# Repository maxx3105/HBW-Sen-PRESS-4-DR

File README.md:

# HBW-Sen-PRESS-4-DR

HomeMatic-Wired-Drucksensormodul für Hutschienenmontage

## Überblick

HomeMatic-Wired-Gerät (RS485) zur Überwachung hydraulischer Drücke mit
Industrie-Drucksensoren. Es stellt 4 analoge Sensoreingänge bereit (A0–A3).
Nicht belegte Kanäle werden in der CCU über `Sensortyp = NICHT_BELEGT` abgeschaltet.

### Basiert auf:
- **HBWired** von Thorsten Pferdekaemper: https://github.com/ThorstenPferdekaemper/HBWired
- **HB-UNI-Sen-PRESS** von jp112sdl: https://github.com/jp112sdl/HB-UNI-Sen-PRESS

## Aufbau des Repositories

```
HBW-Sen-PRESS-4-DR/
├── HBW-Sen-PRESS-4-DR/            Arduino-Sketch (Ordnername muss zur .ino passen)
│   ├── HBW-Sen-PRESS-4-DR.ino
│   ├── HBW-Sen-PRESS-4-DR_config_example.h   Pins, EepromPtr, USE_HARDWARE_SERIAL
│   ├── HBWAnalogPRESS.h
│   └── HBWAnalogPRESS.cpp
├── hbw-sen-press-4-dr.xml         CCU-Gerätedefinition (hs485types)
├── HBW-Sen-PRESS-4_Platine1/    KiCad-Projekt Hauptplatine (+ Gerber)
├── HBW-Sen-PRESS-4_Platine2/    KiCad-Projekt zweite Platine (+ Gerber)
├── BUGFIXES.md                  was in v0.01–v0.03 defekt war und warum
└── CLAUDE.md                    kompakter Projektstand / Übergabenotizen
```

## Hardware

### Unterstützte Sensoren
- **0,5 MPa** Hydraulik-Drucksensor (0–5 bar / 0–72,5 PSI)
- **1,2 MPa** Hydraulik-Drucksensor (0–12 bar / 0–174 PSI)

Beide liefern ein Analogsignal von **0,5 V bis 4,5 V**:
- 0,5 V = 0 bar
- 4,5 V = Endwert (5 bzw. 12 bar je nach Sensortyp)

### Bauteile
- **ATmega328P** Mikrocontroller (alternativ Arduino Nano)
- **MAX487E** RS485-Transceiver
- **MC34063AD** Step-Down-Wandler (24 V Bus → 5 V)
- Analogeingänge: A0–A3 in Verwendung

### Merkmale der Platine
- Hutschienenmontage
- Identify-LED zum Auffinden im Verteiler (blinkt, solange `IDENTIFY_LED` in
  den Geräteparametern gesetzt ist)
- RS485-Busanschluss (A, B, GND, +24 V)
- Schraubklemmen für die Sensoren
- ISP-Programmierstecker
- Status-LED
- Taster für Werksreset

## Pinbelegung

| Pin | Funktion |
|-----|----------|
| A0–A3 | Analogeingänge der Drucksensoren |
| D3 | RS485 TXEN |
| A6 | Taster für Werksreset |
| D12 | Identify-LED (optional, auskommentieren wenn nicht bestückt) |
| D13 | Status-LED |

Pins, `EepromPtr` und `USE_HARDWARE_SERIAL` stehen in
`HBW-Sen-PRESS-4-DR_config_example.h`. Bei abweichender Hardware die Datei
kopieren und die Kopie im Sketch einbinden — dann überschreibt sie eine neue
Version aus GitHub nicht.

## Funktionsumfang

### Konfiguration je Kanal (in CCU/FHEM)

| Parameter | Bereich | Vorgabe | Bedeutung |
|-----------|---------|---------|-----------|
| **Sensortyp** | 0.5MPa / 1.2MPa / NICHT_BELEGT | NICHT_BELEGT | Sensortyp wählen oder Kanal abschalten |
| **SEND_DELTA_VALUE** | 0,0–2,54 bar | 0,1 bar | Sendet, sobald sich der Druck um diesen Betrag ändert |
| **OFFSET** | −1,27 bis +1,27 bar | 0,0 bar | Kalibrier-Offset (vorzeichenbehaftet, mit Bias 127 gespeichert) |
| **UPDATE_INTERVAL** | 1–254 s | 30 s | Pause zwischen zwei Messreihen |
| **SEND_MIN_INTERVAL** | 10–3600 s | 30 s | Mindestabstand zwischen zwei Sendungen |
| **SEND_MAX_INTERVAL** | 10–3600 s | 600 s | Spätestens nach dieser Zeit wird gesendet |

Die Obergrenzen vermeiden den Wert aus lauter Einsen (`0xFF` / `0xFFFF`) — der
markiert eine gelöschte EEPROM-Zelle und wird stattdessen auf die Vorgabe
abgebildet.

### Ablauf

1. **Messung**: alle SAMPLE_INTERVAL (3 s) ein ADC-Wert, gemittelt über
   MAX_SAMPLES (4) — ohne blockierendes `delay()`, damit der RS485-Empfang
   reaktionsfähig bleibt. Nach einer vollständigen Messreihe pausiert der Kanal
   für UPDATE_INTERVAL.
2. **Umrechnung**: ADC → Spannung → Druck (abhängig vom Sensortyp)
3. **Kalibrierung**: OFFSET anwenden
4. **Sendeentscheidung** (in jedem Schleifendurchlauf geprüft, unabhängig vom
   Messzyklus):
   - Mindestens SEND_MIN_INTERVAL seit der letzten Sendung abwarten
   - Senden, wenn sich der Druck um ≥ SEND_DELTA_VALUE geändert hat
   - Nach SEND_MAX_INTERVAL in jedem Fall senden
   - Bei `BUS_BUSY` bleibt der Messwert offen, statt als gesendet zu gelten

Ein vollständiger Messwert entsteht damit alle
`(MAX_SAMPLES − 1) × SAMPLE_INTERVAL + UPDATE_INTERVAL` Sekunden, mit den
Vorgabewerten also alle 39 s. `UPDATE_INTERVAL` ist die Pause *zwischen* den
Messreihen, nicht die Messrate — auf 1 s gestellt misst das Gerät alle 10 s.

## Installation

### 1. Arduino-IDE vorbereiten
```bash
git clone https://github.com/ThorstenPferdekaemper/HBWired
# nach Arduino/libraries/HBWired kopieren
```

### 2. Übersetzen und flashen

Der Sketch liegt im Unterordner `HBW-Sen-PRESS-4-DR/` (der Ordnername muss dem
`.ino`-Namen entsprechen).

- `HBW-Sen-PRESS-4-DR/HBW-Sen-PRESS-4-DR.ino` in der Arduino-IDE öffnen
- Board: **Arduino Nano** (ATmega328P)
- Betriebsart im Konfig-Header wählen: `USE_HARDWARE_SERIAL` gesetzt =
  Produktivbetrieb (RS485 über die Hardware-UART, keine Debug-Ausgabe),
  auskommentiert = Debug über USB und RS485 über SoftwareSerial
- Flashen über ISP oder Bootloader

Oder aus dem Projektverzeichnis heraus:

```
arduino-cli compile --fqbn arduino:avr:nano:cpu=atmega328 HBW-Sen-PRESS-4-DR
arduino-cli compile --fqbn arduino:avr:nano:cpu=atmega328 --upload --programmer usbasp HBW-Sen-PRESS-4-DR
```

Hinweis: Ist die EESAVE-Fuse nicht gesetzt, löscht jeder ISP-Flash das EEPROM —
und damit die Busadresse.

### 3. CCU/RaspberryMatic einrichten
1. `hbw-sen-press-4-dr.xml` auf die CCU kopieren
2. Gerätedefinition einbinden (Addon bzw. FHEM)
3. Gerät an den RS485-Bus anschließen
4. Anlernen und aus dem Posteingang übernehmen

## EEPROM-Belegung

`HBWDevice` liest die Konfigurationsstruktur ab EEPROM-Adresse `0x01`
(siehe `readConfig()` in HBWired.cpp), Struktur-Offset 6 landet also auf `0x07`.

```
0x00      : Gerätetyp (0x50)
0x01      : Logging-Zeit
0x02-0x05 : Zentralen-Adresse
0x06      : Bit 0 Direct-Link-Flag, Bit 1 Identify-LED (invertiert: 1 = aus)
0x07      : Kanal 1, Konfiguration (8 Byte)
  +0: send_delta_value
  +1: offset (Bias 127: 0 = −1,27 bar, 127 = 0,00 bar, 254 = +1,27 bar)
  +2-3: send_max_interval (16 Bit, little endian)
  +4-5: send_min_interval (16 Bit, little endian)
  +6: update_interval
  +7: pressure_sensor_type
0x0F/0x17/0x1F : Kanal 2..4, Konfiguration
0x3FC-0x3FF : OWN_ADDRESS (Busadresse, E2END−3 beim 1-kB-EEPROM des 328P)
```

Die Belegung ist über drei `static_assert` in
`HBW-Sen-PRESS-4-DR/HBW-Sen-PRESS-4-DR.ino` an die XML gekoppelt — Strukturgröße,
Startoffset der Kanäle und der Abstand zu `OWN_ADDRESS` müssen passen,
sonst bricht der Build.

## Fehlersuche

### Keine Messwerte / alles null
- Verdrahtung prüfen (3-adrig: VCC, GND, Signal)
- Liefert der Sensor tatsächlich 0,5–4,5 V?
- Ist der Kanal freigegeben (`Sensortyp` ≠ `NICHT_BELEGT`)? Bei abgeschaltetem
  Kanal wird weder gemessen noch gesendet.

### Falsche Druckwerte
- Richtigen Sensortyp gewählt (0,5 MPa vs. 1,2 MPa)?
- Zur Kalibrierung den Parameter OFFSET verwenden
- VCC muss *nicht* exakt 5,0 V betragen: Die Sensoren arbeiten ratiometrisch,
  ihr Ausgang skaliert mit der Versorgung. Hängen Sensor und ADC an derselben
  5-V-Schiene, hebt sich die Abweichung des Reglers auf — deshalb wird die
  VCC-Referenz des ADC benutzt und nicht die interne 1,1-V-Referenz.
  Wichtig ist nur, dass Sensor und MCU aus **derselben** Schiene versorgt werden.

### Gerät kommuniziert nicht
- RS485-Verdrahtung prüfen (A/B nicht vertauscht)
- TX/RX-Aktivität beobachten

## Lizenz

Creative Commons BY-NC-SA 3.0 AT
http://creativecommons.org/licenses/by-nc-sa/3.0/at/

## Dank an

- Thorsten Pferdekaemper – HBWired-Framework
- Dirk Hoffmann – Beiträge zu HBWired
- jp112sdl – ursprüngliches Konzept HB-UNI-Sen-PRESS

## Änderungsverlauf

### v0.05
- Gerät in HBW-Sen-PRESS-4-DR umbenannt (Typ-Byte bleibt 0x50; wegen des
  Namenswechsels in der CCU löschen und neu anlernen)
- Pinbelegung, `EepromPtr` und `USE_HARDWARE_SERIAL` in einen Konfig-Header
  ausgelagert
- Identify-LED ergänzt

### v0.04
- Kanalzahl auf 4 festgelegt (A0–A3)

### v0.01 (02.04.2024)
- Erste Fassung auf Basis von HB-UNI-Sen-PRESS
- CCU-Anbindung über XML

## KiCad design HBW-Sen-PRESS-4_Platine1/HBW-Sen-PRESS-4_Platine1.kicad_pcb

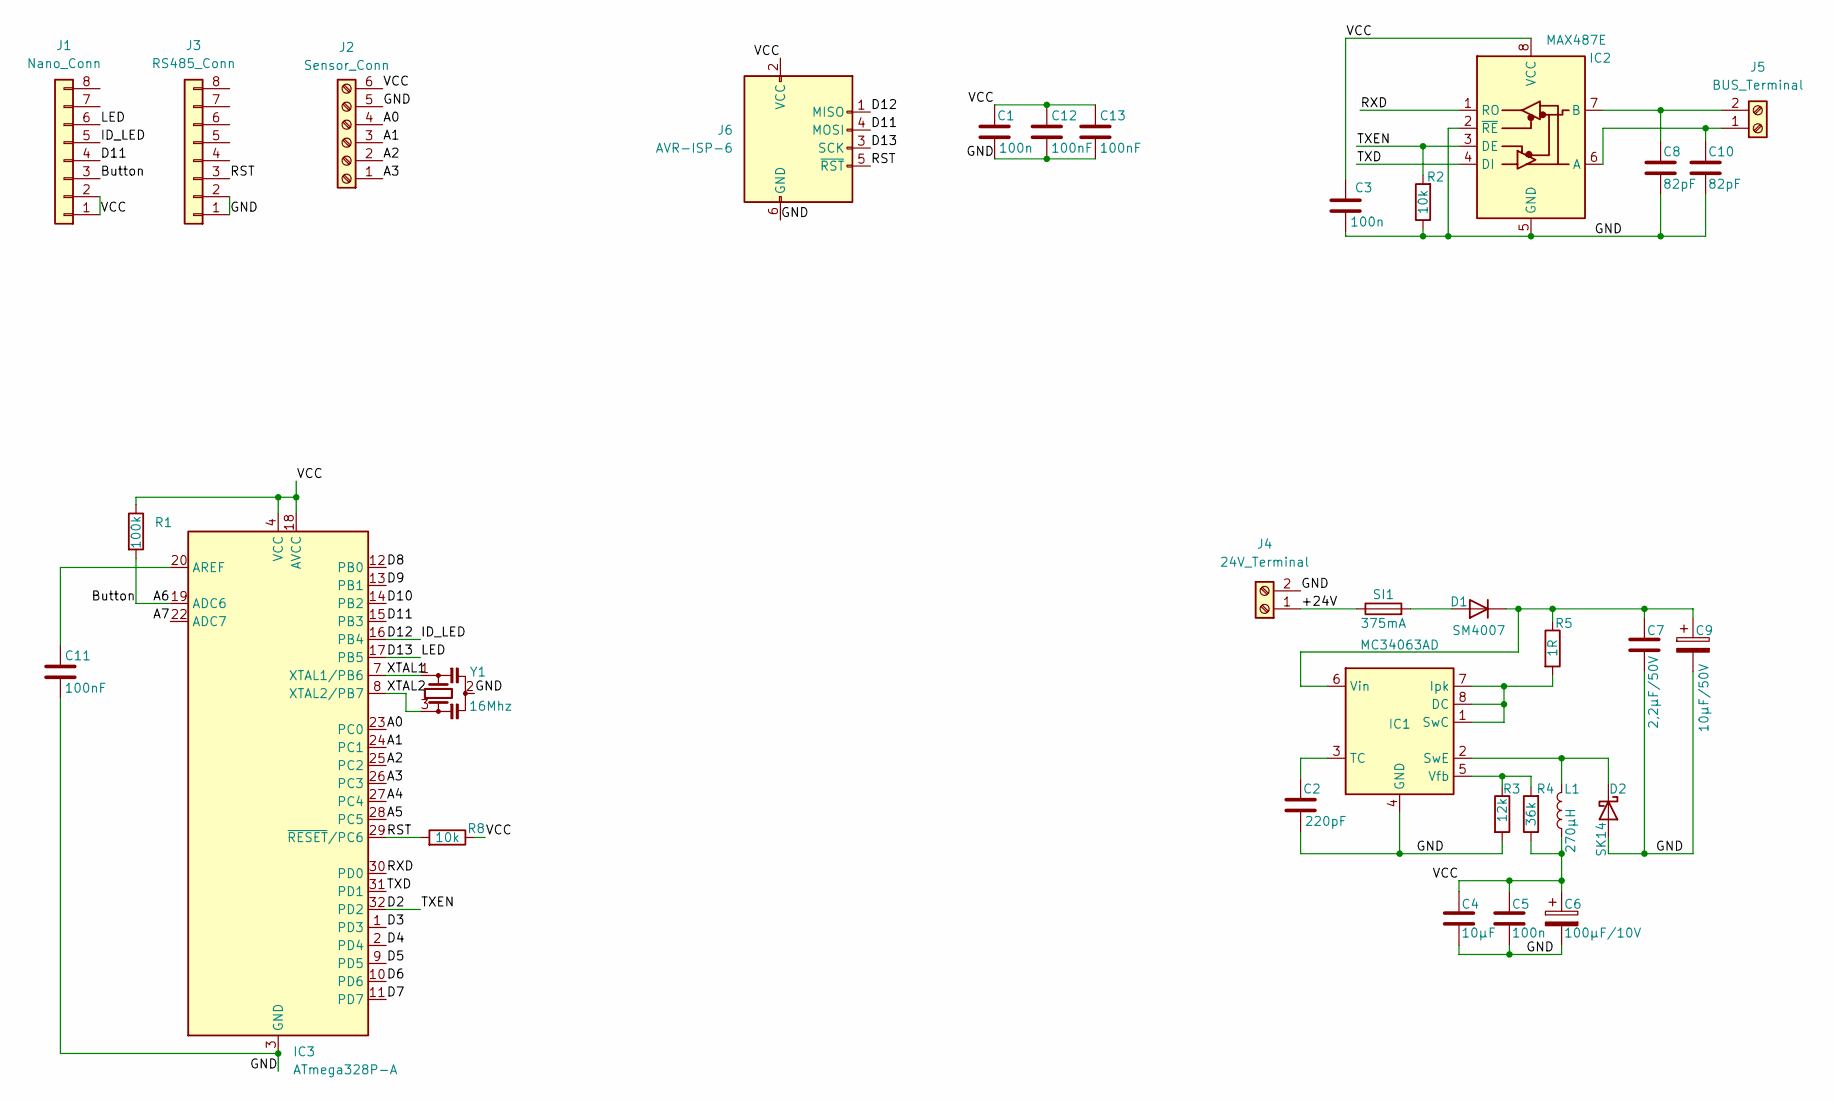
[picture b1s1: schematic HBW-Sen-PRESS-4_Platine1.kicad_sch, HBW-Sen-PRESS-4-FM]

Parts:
C1, C3, C5: 100n; C_0805_2012Metric_Pad1.18x1.45mm_HandSolder
C2: 220pF; C_0805_2012Metric_Pad1.18x1.45mm_HandSolder
C4: 10µF; C_1210_3225Metric_Pad1.33x2.70mm_HandSolder
C6: 100µF/10V; CP_Radial_D5.0mm_P2.50mm
C7: 2,2µF/50V; C_1210_3225Metric_Pad1.33x2.70mm_HandSolder
C8, C10: 82pF; C_0805_2012Metric_Pad1.18x1.45mm_HandSolder
C9: 10µF/50V; CP_Radial_D5.0mm_P2.50mm
C11, C12, C13: 100nF; C_0805_2012Metric_Pad1.18x1.45mm_HandSolder
D1: SM4007; D_MELF
D2: SK14; D_SMA_Handsoldering
IC1: MC34063AD; SOIC-8_3.9x4.9mm_P1.27mm
IC2: MAX487E; SOIC-8_3.9x4.9mm_P1.27mm
IC3: ATmega328P-A; TQFP-32_7x7mm_P0.8mm
J1: Nano_Conn; PinHeader_1x08_P2.54mm_Vertical
J2: Sensor_Conn; TerminalBlock_CUI_TB007-508-06_1x06_P5.08mm_Horizontal
J3: RS485_Conn; PinHeader_1x08_P2.54mm_Vertical
J4: 24V_Terminal; TerminalBlock_bornier-2_P5.08mm
J5: BUS_Terminal; TerminalBlock_bornier-2_P5.08mm
J6: AVR-ISP-6; PinHeader_2x03_P2.54mm_ISP
L1: 270µH; L_Taiyo-Yuden_MD-4040
R1: 100k; R_0805_2012Metric_Pad1.20x1.40mm_HandSolder
R2, R8: 10k; R_0805_2012Metric_Pad1.20x1.40mm_HandSolder
R3: 12k; R_0805_2012Metric_Pad1.20x1.40mm_HandSolder
R4: 36k; R_0805_2012Metric_Pad1.20x1.40mm_HandSolder
R5: 1R; R_0805_2012Metric_Pad1.20x1.40mm_HandSolder
SI1: 375mA; FUSC6127X294N
Y1: 16Mhz; Resonator_SMD_Murata_CSTxExxV-3Pin_3.0x1.1mm_HandSoldering

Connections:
/+24V: J4.1, SI1.1
/A0: IC3.23 (PC0), J2.4
/A1: IC3.24 (PC1), J2.3
/A2: IC3.25 (PC2), J2.2
/A3: IC3.26 (PC3), J2.1
/A4: IC3.27 (PC4)
/A5: IC3.28 (PC5)
/A6: IC3.19 (ADC6), J1.3, R1.2
/A7: IC3.22 (ADC7)
/D2: IC2.3 (DE), IC3.32 (PD2), R2.2
/D3: IC3.1 (PD3)
/D4: IC3.2 (PD4)
/D5: IC3.9 (PD5)
/D6: IC3.10 (PD6)
/D7: IC3.11 (PD7)
/D8: IC3.12 (PB0)
/D9: IC3.13 (PB1)
/D10: IC3.14 (PB2)
/D11: IC3.15 (PB3), J1.4, J6.4 (MOSI)
/D12: IC3.16 (PB4), J1.5, J6.1 (MISO)
/D13: IC3.17 (PB5), J1.6, J6.3 (SCK)
/GND: C1.2, C2.2, C3.1, C4.2, C5.1, C6.2, C7.2, C8.2, C9.2, C10.2, C11.1, C12.1, C13.1, D2.2 (A), IC1.4 (GND), IC2.2 (~RE), IC2.5 (GND), IC3.3 (GND), IC3.5 (GND), IC3.21 (GND), J2.5, J3.1, J3.2, J4.2, J6.6 (GND), R2.1, R3.2, Y1.2
/RST: IC3.29 (~RESET/PC6), J3.3, J6.5 (~RST), R8.2
/RXD: IC2.1 (RO), IC3.30 (PD0)
/TXD: IC2.4 (DI), IC3.31 (PD1)
/VCC: C1.1, C3.2, C4.1, C5.2, C6.1, C12.2, C13.2, IC2.8 (VCC), IC3.4 (VCC), IC3.6 (VCC), IC3.18 (AVCC), J1.1, J1.2, J2.6, J6.2 (VCC), L1.1, R1.1, R4.1, R8.1
/XTAL1: IC3.7 (XTAL1/PB6), Y1.1
/XTAL2: IC3.8 (XTAL2/PB7), Y1.3
unnamed: D1.2 (A), SI1.2
unnamed: C7.1, C9.1, D1.1 (K), IC1.6 (Vin), R5.1
unnamed: D2.1 (K), IC1.2 (SwE), L1.2
unnamed: IC1.1 (SwC), IC1.7 (Ipk), IC1.8 (DC), R5.2
unnamed: C2.1, IC1.3 (TC)
unnamed: IC1.5 (Vfb), R3.1, R4.2
unnamed: C10.1, IC2.6 (A), J5.1
unnamed: C8.1, IC2.7 (B), J5.2
unnamed: C11.2, IC3.20 (AREF)

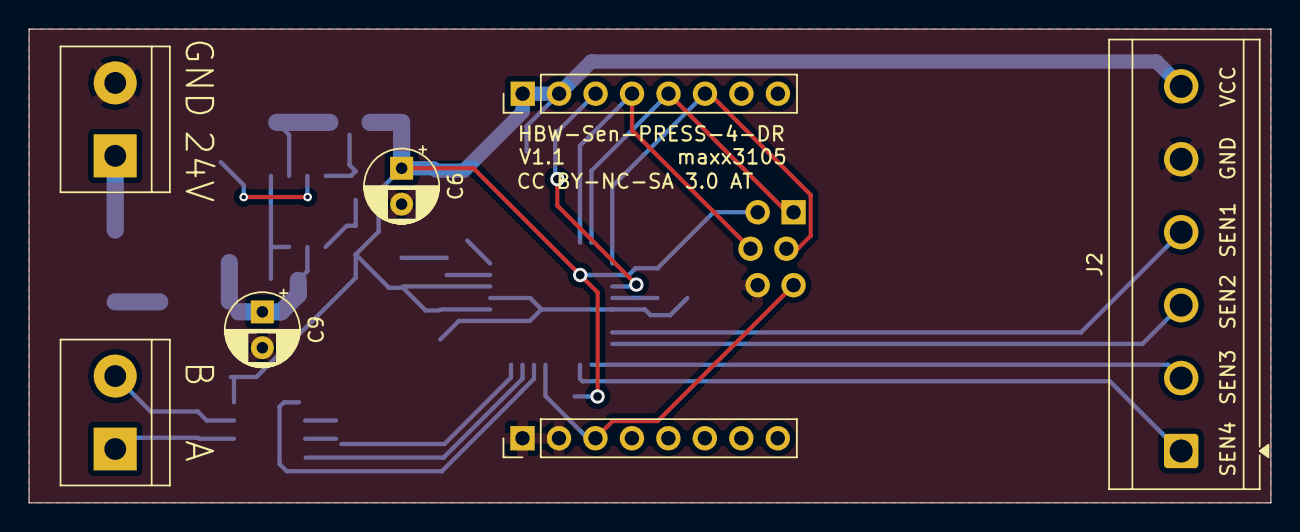
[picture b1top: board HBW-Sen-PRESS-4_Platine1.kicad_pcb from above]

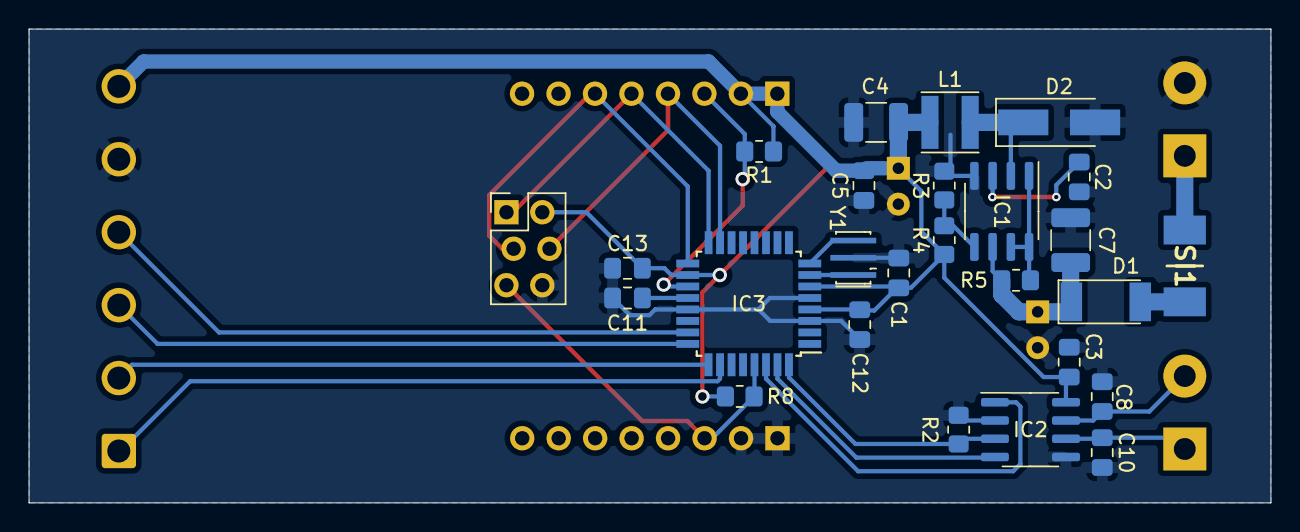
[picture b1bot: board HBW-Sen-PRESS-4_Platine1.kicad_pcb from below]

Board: 2 copper layers, 86.5 x 33.0 mm, 33 parts (26 on the bottom side), 26 nets.

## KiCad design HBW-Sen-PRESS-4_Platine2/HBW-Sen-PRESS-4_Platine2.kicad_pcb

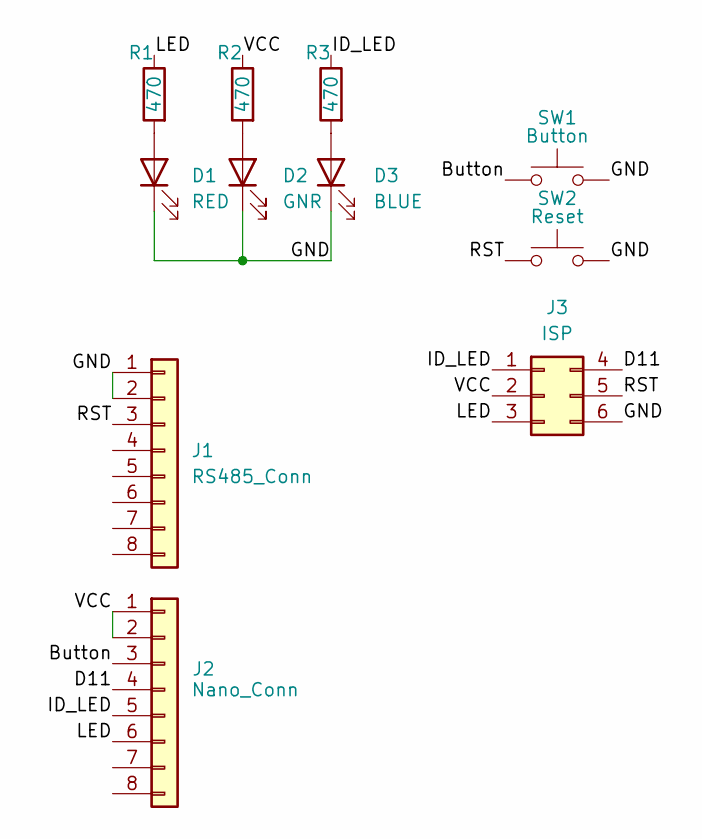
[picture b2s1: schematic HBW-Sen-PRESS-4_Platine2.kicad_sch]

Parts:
D1: RED; LED_D5.0mm
D2: GNR; LED_D5.0mm
D3: BLUE; LED_D5.0mm
J1: RS485_Conn; PinHeader_1x08_P2.54mm_Vertical
J2: Nano_Conn; PinSocket_1x08_P2.54mm_Vertical
J3: ISP; PinHeader_2x03_P2.54mm_Vertical
R1, R2, R3: 470; R_0805_2012Metric_Pad1.20x1.40mm_HandSolder
SW1: Button; SW_PUSH_6mm_H13mm
SW2: Reset; SW_PUSH_6mm_H13mm

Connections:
/Button: J2.3, SW1.1
/D11: J2.4, J3.4
/GND: D1.1 (K), D2.1 (K), D3.1 (K), J1.1, J1.2, J3.6, SW1.2, SW2.2
/ID_LED: J2.5, J3.1, R3.1
/LED: J2.6, J3.3, R1.1
/RST: J1.3, J3.5, SW2.1
/VCC: J2.1, J2.2, J3.2, R2.1
unnamed: D1.2 (A), R1.2
unnamed: D2.2 (A), R2.2
unnamed: D3.2 (A), R3.2

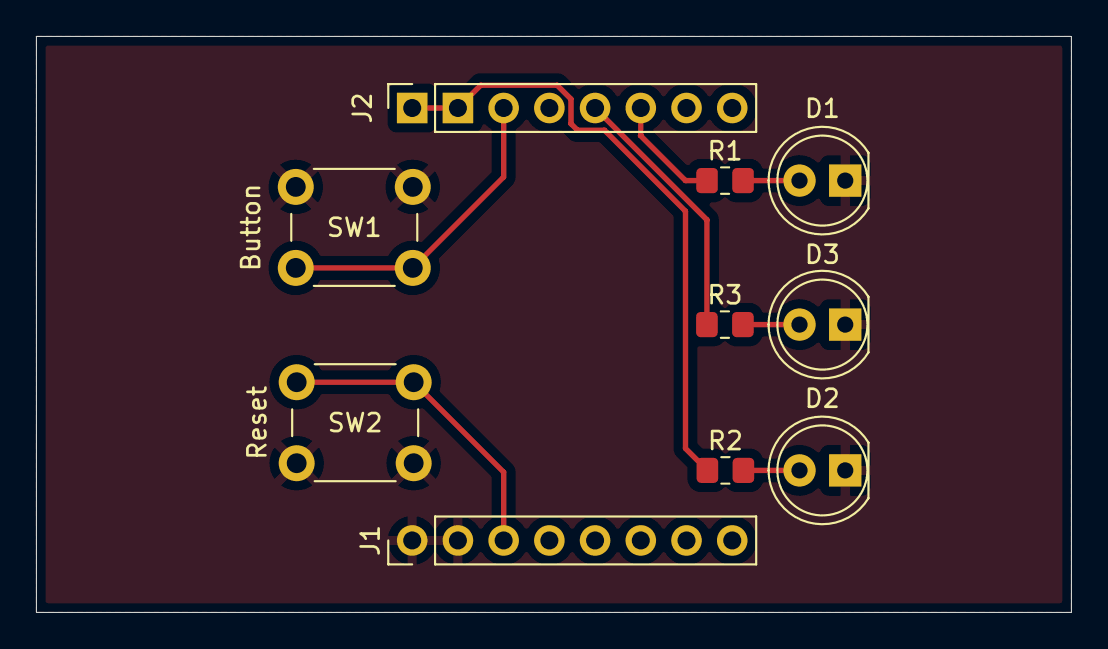
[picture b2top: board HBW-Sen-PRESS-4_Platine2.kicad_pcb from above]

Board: 2 copper layers, 57.5 x 32.0 mm, 10 parts (0 on the bottom side), 9 nets.

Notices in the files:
HBW-Sen-PRESS-4_Platine1/HBW-Sen-PRESS-4_Platine1.kicad_pcb:
CC BY-NC-SA 3.0 AT
